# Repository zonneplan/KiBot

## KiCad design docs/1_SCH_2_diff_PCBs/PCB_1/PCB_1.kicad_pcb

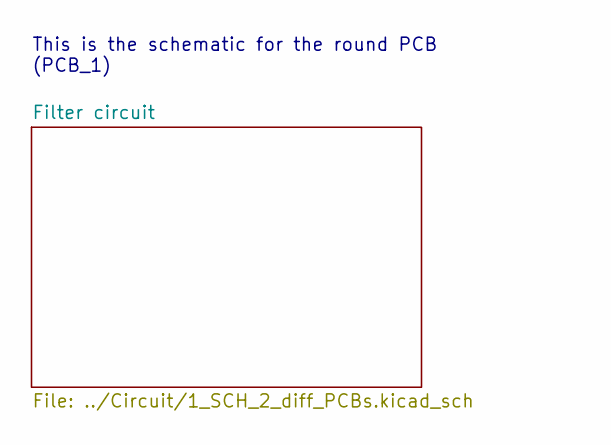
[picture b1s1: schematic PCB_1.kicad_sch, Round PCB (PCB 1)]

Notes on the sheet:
This is the schematic for the round PCB (PCB_1)

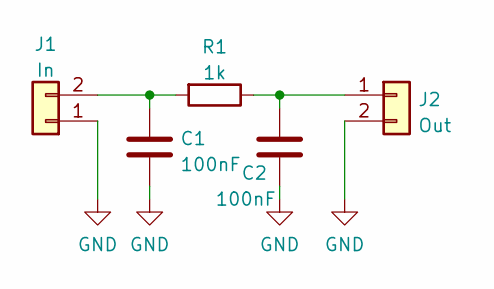
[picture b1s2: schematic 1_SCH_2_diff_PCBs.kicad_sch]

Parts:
C1, C2: 100nF; C_Disc_D3.0mm_W1.6mm_P2.50mm
J1: In; Molex_KK-254_AE-6410-02A_1x02_P2.54mm_Vertical
J2: Out; Molex_KK-254_AE-6410-02A_1x02_P2.54mm_Vertical
R1: 1k; R_Axial_DIN0207_L6.3mm_D2.5mm_P7.62mm_Horizontal

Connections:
GND: C1.2, C2.2, J1.1, J2.2
unnamed: C1.1, J1.2, R1.2
unnamed: C2.1, J2.1, R1.1

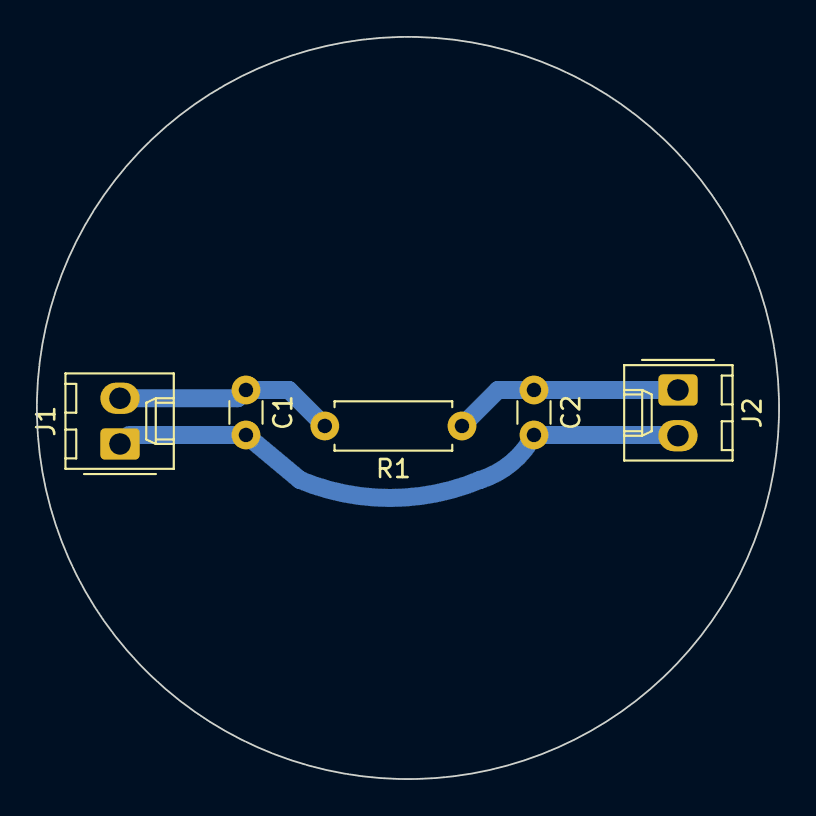
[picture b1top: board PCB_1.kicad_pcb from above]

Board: 2 copper layers, 41.2 x 41.2 mm, 5 parts (0 on the bottom side), 3 nets.

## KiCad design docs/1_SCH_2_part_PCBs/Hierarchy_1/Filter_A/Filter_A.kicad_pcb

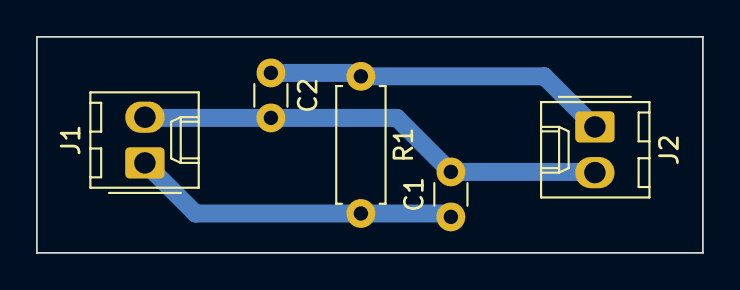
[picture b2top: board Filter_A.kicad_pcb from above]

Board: 2 copper layers, 37.0 x 12.0 mm, 5 parts (0 on the bottom side), 3 nets.

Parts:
C1, C2: 100nF; C_Disc_D3.0mm_W1.6mm_P2.50mm
J1: In; Molex_KK-254_AE-6410-02A_1x02_P2.54mm_Vertical
J2: Out; Molex_KK-254_AE-6410-02A_1x02_P2.54mm_Vertical
R1: 1k; R_Axial_DIN0207_L6.3mm_D2.5mm_P7.62mm_Horizontal

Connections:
/IN: C1.1, J1.1, R1.2
/OUT: C2.1, J2.1, R1.1
GND1: C1.2, C2.2, J1.2, J2.2

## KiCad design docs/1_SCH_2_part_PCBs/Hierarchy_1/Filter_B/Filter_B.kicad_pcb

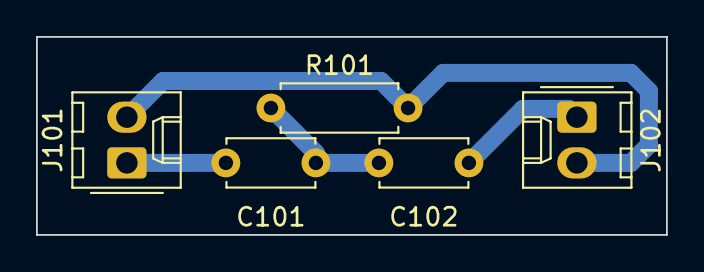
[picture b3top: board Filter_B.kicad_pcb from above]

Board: 2 copper layers, 35.0 x 11.0 mm, 5 parts (0 on the bottom side), 4 nets.

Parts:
C101, C102: 100nF; C_Disc_D4.7mm_W2.5mm_P5.00mm
J101: IN; Molex_KK-254_AE-6410-02A_1x02_P2.54mm_Vertical
J102: OUT; Molex_KK-254_AE-6410-02A_1x02_P2.54mm_Vertical
R101: 1k; R_Axial_DIN0207_L6.3mm_D2.5mm_P7.62mm_Horizontal

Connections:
/IN: C101.1, J101.1
/OUT: C102.2, J102.1
GND2: J101.2, J102.2, R101.2
unnamed: C101.2, C102.1, R101.1

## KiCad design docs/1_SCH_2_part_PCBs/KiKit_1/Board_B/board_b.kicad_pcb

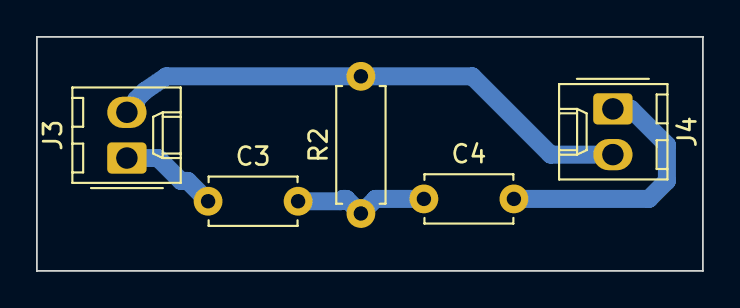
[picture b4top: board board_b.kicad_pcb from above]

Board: 2 copper layers, 37.0 x 13.0 mm, 6 parts (0 on the bottom side), 4 nets.

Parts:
B: Board
C3, C4: 100nF; C_Disc_D4.7mm_W2.5mm_P5.00mm
J3: IN; Molex_KK-254_AE-6410-02A_1x02_P2.54mm_Vertical
J4: OUT; Molex_KK-254_AE-6410-02A_1x02_P2.54mm_Vertical
R2: 1k; R_Axial_DIN0207_L6.3mm_D2.5mm_P7.62mm_Horizontal

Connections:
Board_0-Net-(C3-Pad1): C3.1, J3.1
Board_0-Net-(C3-Pad2): C3.2, C4.1, R2.1
Board_0-Net-(C4-Pad2): C4.2, J4.1
Board_0-Net-(J3-Pad2): J3.2, J4.2, R2.2
